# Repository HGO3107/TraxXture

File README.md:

# 🚀 TaxXture – The Tracker with Capturing Features
A tracking device with **remote interior capturing capabilty**

## 🔥 Features  
- **Real-time location tracking** – Get your vehicle’s location on demand  
- **Motion sensing & speed monitoring** – Know when your vehicle is on the move  
- **Battery Backup and health monitoring** – Keep track of power levels  
- **Remote interior capturing** – Snap image of your vehicle’s interior when needed  
- **Offline storage** – Data backup, even without an internet connection  
- **Reverse polarity protection** – To ensure the device does not get affected should incase the vehicle pollarity is mistakenly swapped  

## 🏗️ Project Structure  
📂 **Main Board** – The brains of the operation
📂 **Cam-Interconnect Board** – The bridge between the camera and the system  
📂 **Rendered Images** – Stunning visuals of the design  

## 🔧 Main Board – What's Inside?  
The **Main Board** packs all the essentials:  
✅ **Microcontroller, sensors, and actuator circuitry**  
✅ **LVDS driver/receiver port** – Ensures **3-5m** long-distance camera communication  

## 📸 Cam-Interconnect Board  
This board connects the camera to the system using:  
✅ **LVDS to SPI converter**  
✅ **Camera port connector**  

## 🚧 Disclaimer; Work in Progress (Status: **DRAFT** 🚀)  
Still some work to do, Below are what I could think of, you can pick it up from here if insterested:  

🔲 **Generate BOM & Fabrication files**  
🔲 **Review schematics & PCB layouts**  
🔲 **Complete the Cam-Interconnect Board:**  
   - PCB layout  
   - Electrical Rule Check (ERC) & Design Rule Check (DRC)  
🔲 **Finalize the enclosure design** (Done in FreeCAD but needs tweaks for connectors)  

## 📷 Main Board Images  

[📄 View Documentation](Hardware/Main-Board/TraxXturE_board.pdf)

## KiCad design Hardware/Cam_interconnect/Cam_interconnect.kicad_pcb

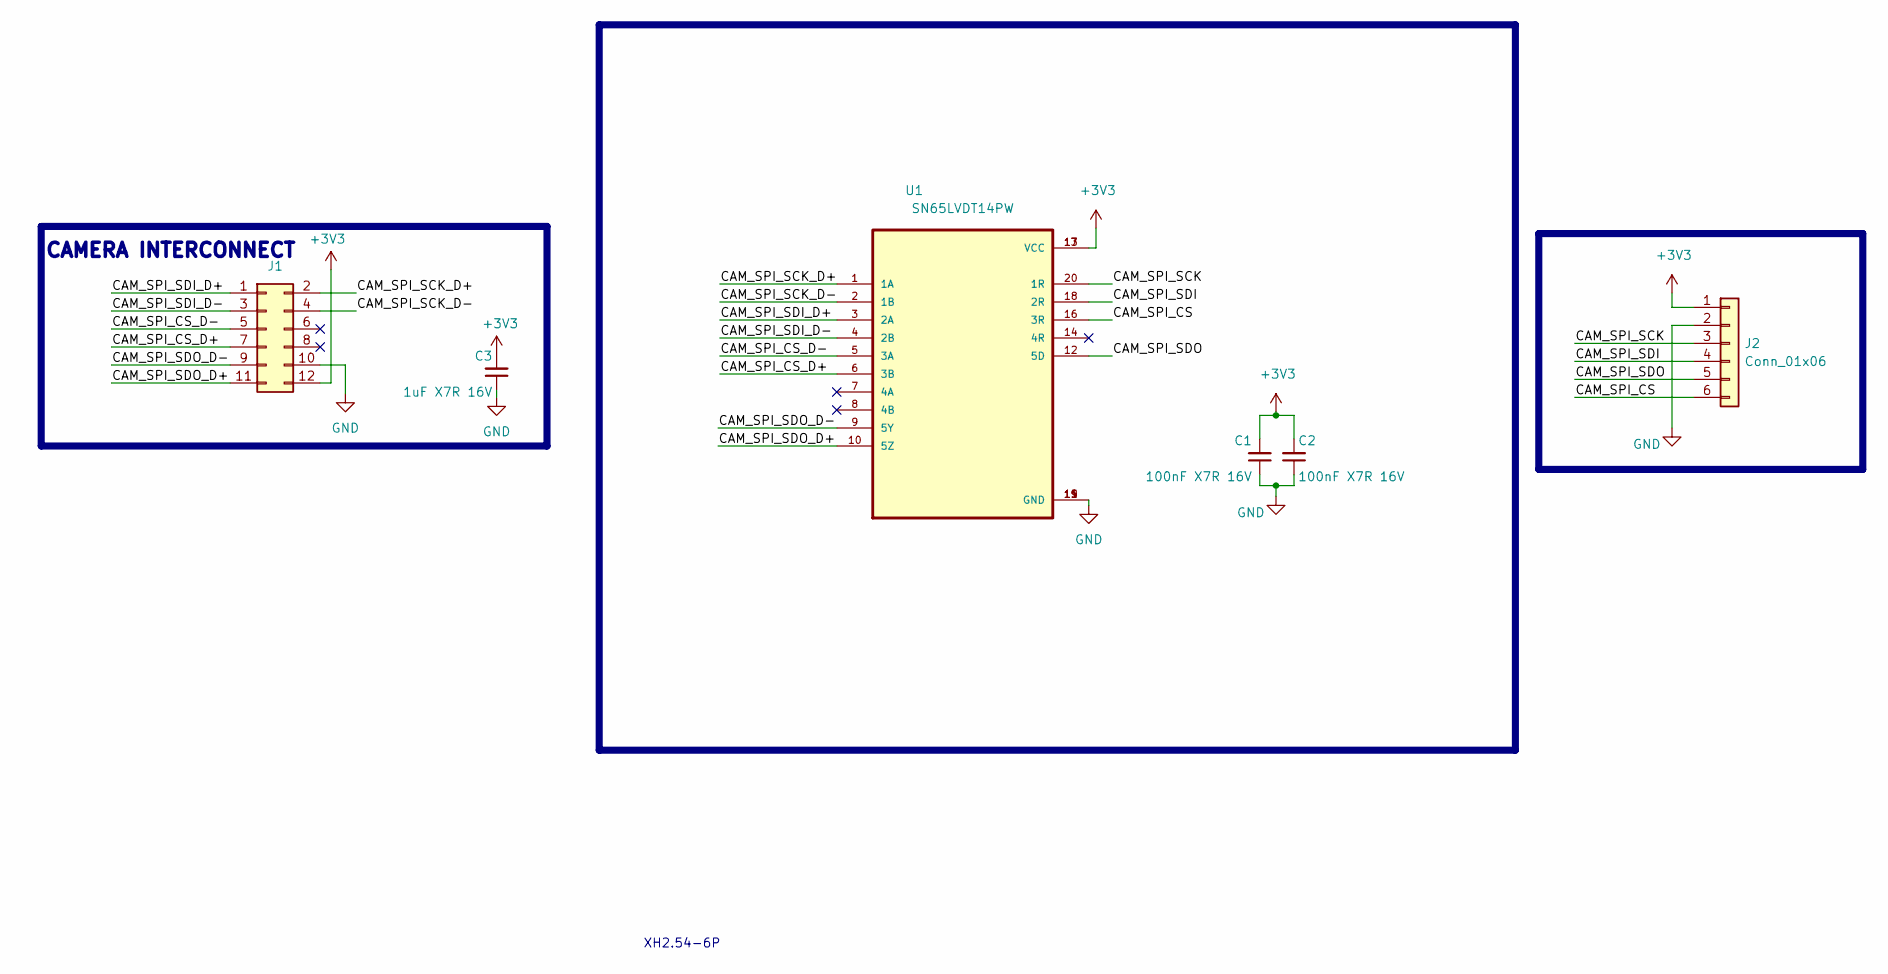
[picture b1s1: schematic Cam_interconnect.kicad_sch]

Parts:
C1, C2: 100nF X7R 16V; C_0402_1005Metric
C3: 1uF X7R 16V; C_0402_1005Metric
J1: Conn_02x06_Odd_Even; JST_PHD_S12B-PHDSS_2x06_P2.00mm_Horizontal
J2: Conn_01x06; PinSocket_1x06_P2.54mm_Vertical_SMD_Pin1Right
U1: SN65LVDT14PW; SOP65P640X120-20N

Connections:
+3V3: C1.2, C2.2, C3.2, J1.12, J2.1, U1.13 (VCC), U1.17 (VCC)
/CAM_SPI_CS: J2.6, U1.16 (3R)
/CAM_SPI_CS_D+: J1.7, U1.6 (3B)
/CAM_SPI_CS_D-: J1.5, U1.5 (3A)
/CAM_SPI_SCK: J2.3, U1.20 (1R)
/CAM_SPI_SCK_D+: J1.2, U1.1 (1A)
/CAM_SPI_SCK_D-: J1.4, U1.2 (1B)
/CAM_SPI_SDI: J2.4, U1.18 (2R)
/CAM_SPI_SDI_D+: J1.1, U1.3 (2A)
/CAM_SPI_SDI_D-: J1.3, U1.4 (2B)
/CAM_SPI_SDO: J2.5, U1.12 (5D)
/CAM_SPI_SDO_D+: J1.11, U1.10 (5Z)
/CAM_SPI_SDO_D-: J1.9, U1.9 (5Y)
GND: C1.1, C2.1, C3.1, J1.10, J2.2, U1.11 (GND), U1.15 (GND), U1.19 (GND)

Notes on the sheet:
XH2.54-6P
CAMERA INTERCONNECT

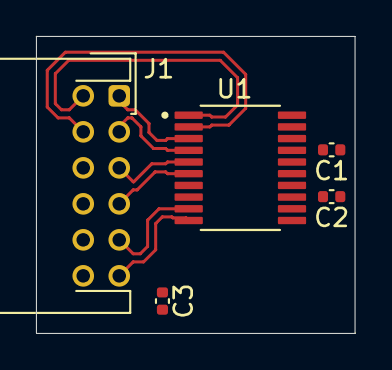
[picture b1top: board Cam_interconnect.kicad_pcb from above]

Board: 4 copper layers, 17.7 x 16.5 mm, 6 parts (1 on the bottom side), 14 nets.

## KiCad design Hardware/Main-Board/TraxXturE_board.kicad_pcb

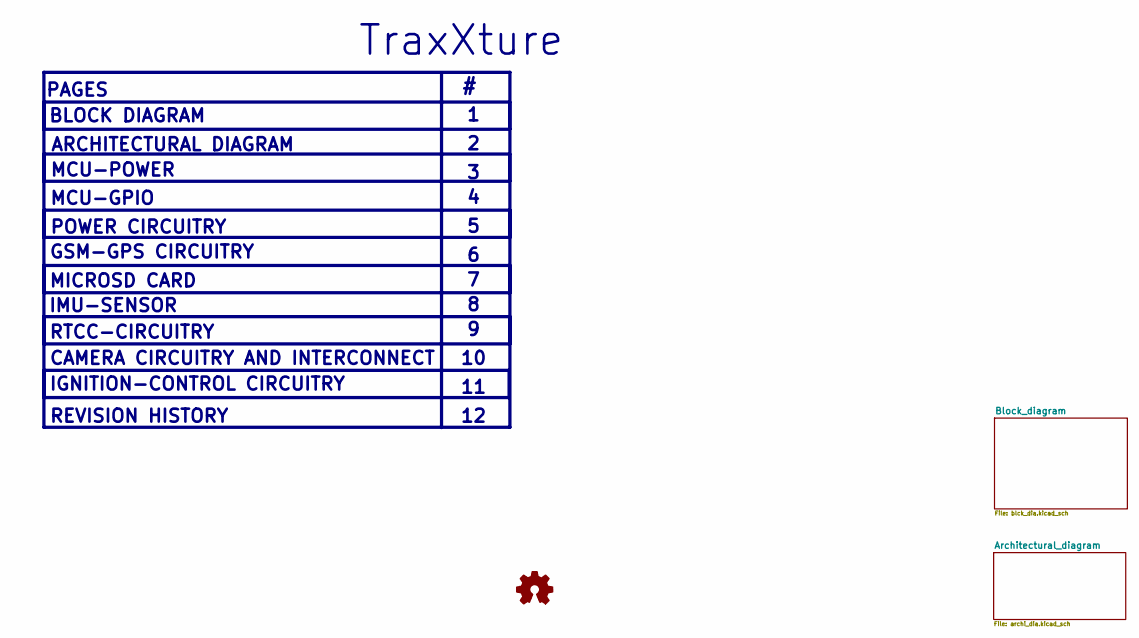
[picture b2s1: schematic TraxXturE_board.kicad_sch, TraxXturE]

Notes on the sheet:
IMU-SENSOR
MCU-POWER
MICROSD CARD
ARCHITECTURAL DIAGRAM
PAGES
RTCC-CIRCUITRY
CAMERA CIRCUITRY AND INTERCONNECT
BLOCK DIAGRAM
POWER CIRCUITRY
GSM-GPS CIRCUITRY
REVISION HISTORY
MCU-GPIO
IGNITION-CONTROL CIRCUITRY
TraxXture

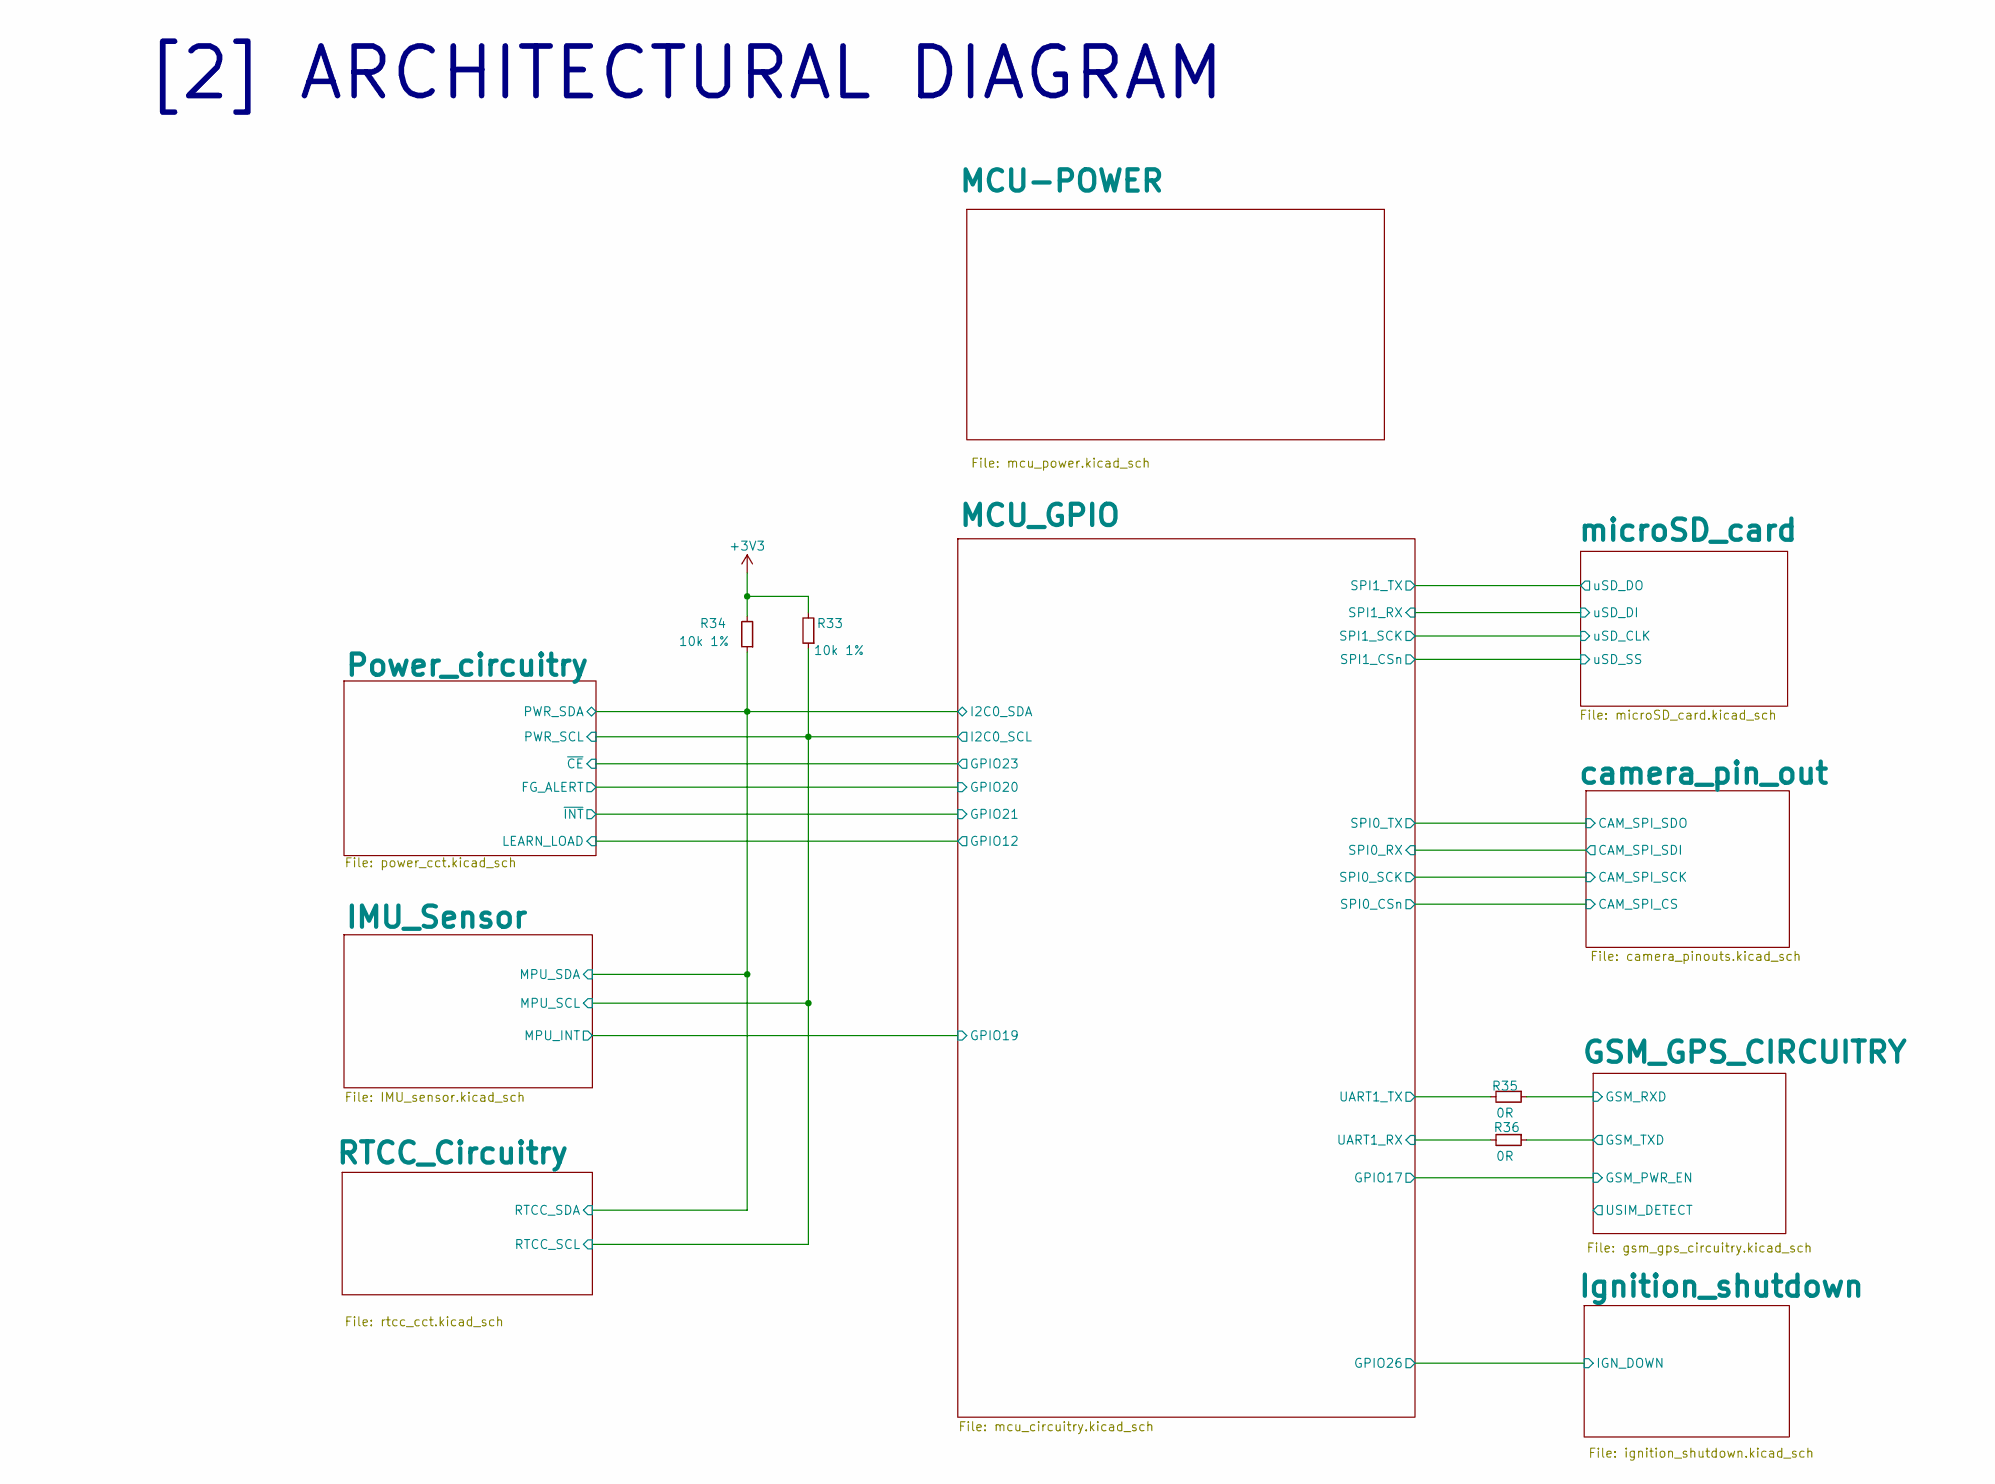
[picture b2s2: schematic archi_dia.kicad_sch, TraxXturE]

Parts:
R33, R34: 10k 1%; R_0402_1005Metric
R35, R36: 0R; R_0402_1005Metric

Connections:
+3V3: R33.2, R34.2; also elsewhere on the board
/Architectural_diagram/GSM_GPS_CIRCUITRY/GSM_RXD: R35.1; also elsewhere on the board
/Architectural_diagram/GSM_GPS_CIRCUITRY/GSM_TXD: R36.1; also elsewhere on the board
/Architectural_diagram/IMU_Sensor/MPU_SCL: R33.1; also elsewhere on the board
/Architectural_diagram/IMU_Sensor/MPU_SDA: R34.1; also elsewhere on the board
/Architectural_diagram/MCU_GPIO/UART1_RX: R36.2; also elsewhere on the board
/Architectural_diagram/MCU_GPIO/UART1_TX: R35.2; also elsewhere on the board

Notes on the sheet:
[2] ARCHITECTURAL DIAGRAM

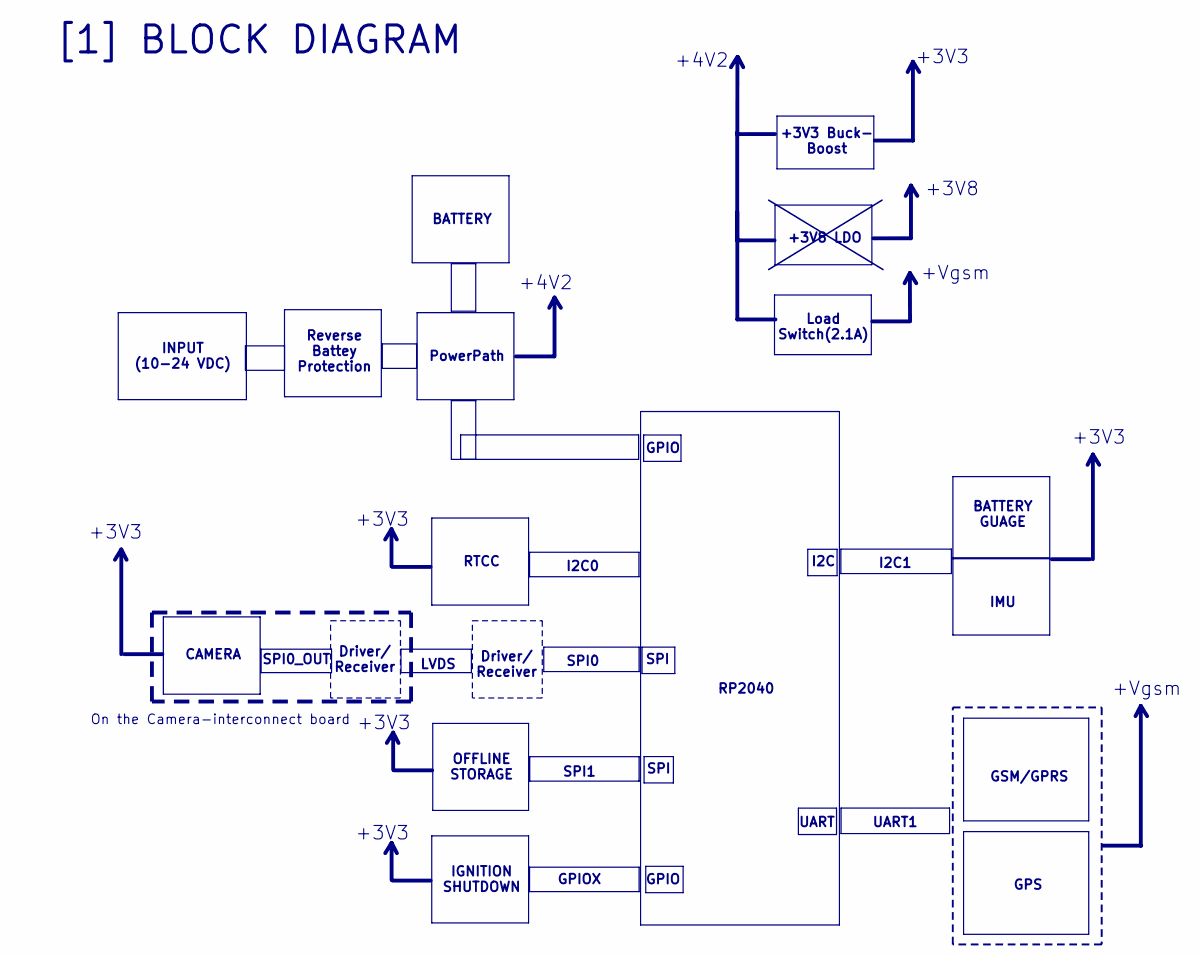
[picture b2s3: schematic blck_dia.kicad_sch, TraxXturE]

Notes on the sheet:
SPI0_OUT
+3V3
SPI
I2C
OFFLINE STORAGE
+3V8
I2C0
GPIO
UART
BATTERY
CAMERA
GSM/GPRS
INPUT (10-24 VDC)
Driver/ Receiver
I2C1
+3V8 LDO
IGNITION SHUTDOWN
BATTERY GUAGE
PowerPath
LVDS
SPI1
+3V3 Buck- Boost
SPI0
Reverse Battey Protection
+4V2
RTCC
On the Camera-interconnect board
+Vgsm
UART1
[1] BLOCK DIAGRAM
GPS
IMU
RP2040
GPIOX
Load Switch(2.1A)

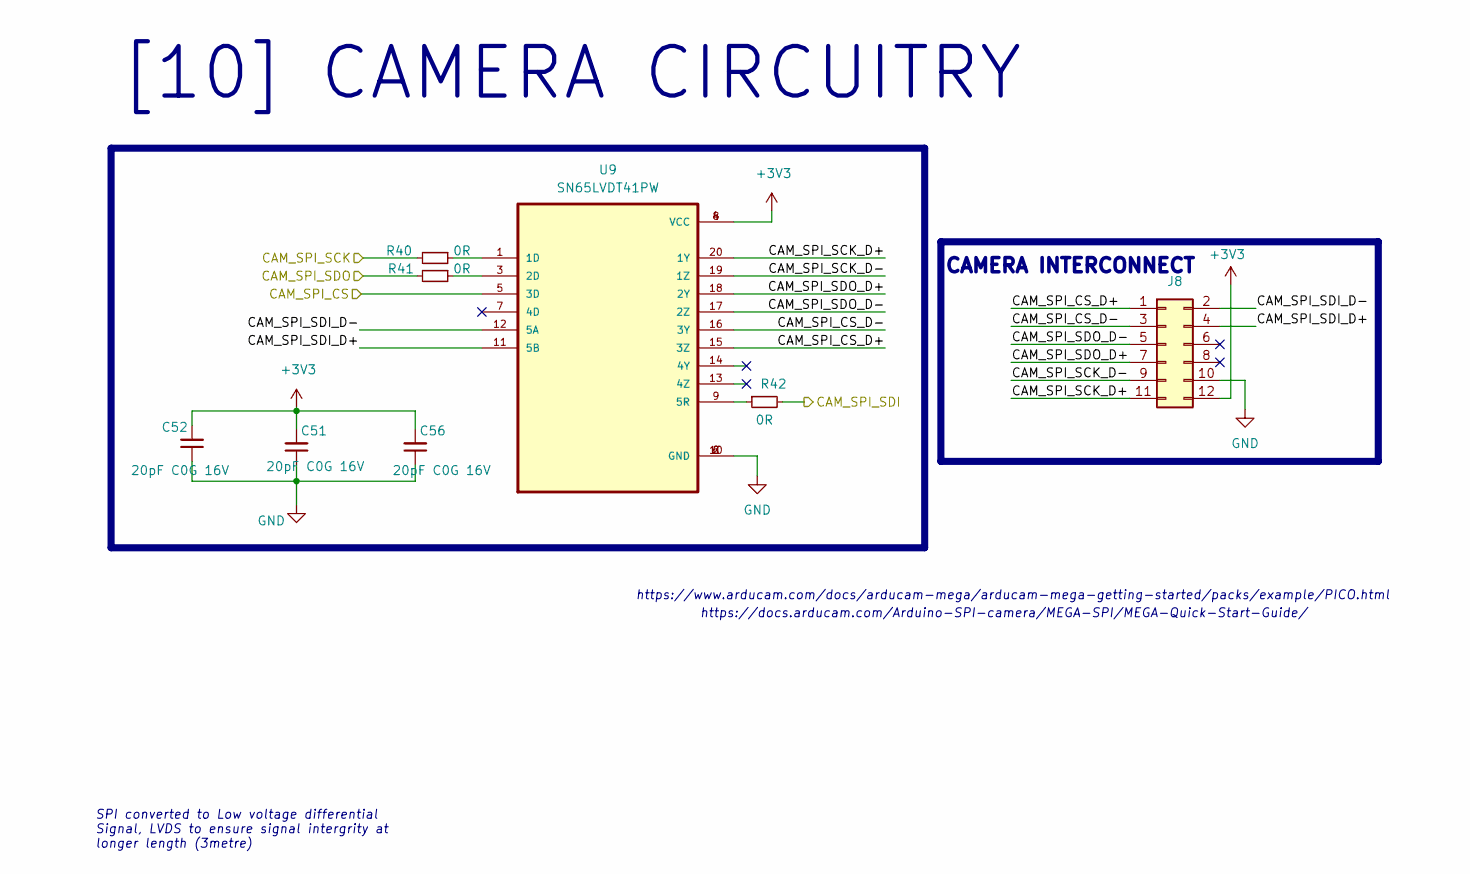
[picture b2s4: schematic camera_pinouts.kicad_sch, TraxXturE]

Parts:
C51, C52, C56: 20pF C0G 16V; C_0402_1005Metric
J8: Conn_02x06_Odd_Even; JST_PHD_S12B-PHDSS_2x06_P2.00mm_Horizontal
R40, R41, R42: 0R; R_0402_1005Metric
U9: SN65LVDT41PW; SOP65P640X120-20N

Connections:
+3V3: C51.2, C52.2, C56.2, J8.12, U9.4 (VCC), U9.8 (VCC); also elsewhere on the board
/Architectural_diagram/MCU_GPIO/SPI0_CSn: U9.5 (3D); also elsewhere on the board
/Architectural_diagram/MCU_GPIO/SPI0_RX: R42.2; also elsewhere on the board
/Architectural_diagram/MCU_GPIO/SPI0_SCK: R40.2; also elsewhere on the board
/Architectural_diagram/MCU_GPIO/SPI0_TX: R41.2; also elsewhere on the board
/Architectural_diagram/camera_pin_out/CAM_SPI_CS_D+: J8.1, U9.15 (3Z)
/Architectural_diagram/camera_pin_out/CAM_SPI_CS_D-: J8.3, U9.16 (3Y)
/Architectural_diagram/camera_pin_out/CAM_SPI_SCK_D+: J8.11, U9.20 (1Y)
/Architectural_diagram/camera_pin_out/CAM_SPI_SCK_D-: J8.9, U9.19 (1Z)
/Architectural_diagram/camera_pin_out/CAM_SPI_SDI_D+: J8.4, U9.11 (5B)
/Architectural_diagram/camera_pin_out/CAM_SPI_SDI_D-: J8.2, U9.12 (5A)
/Architectural_diagram/camera_pin_out/CAM_SPI_SDO_D+: J8.7, U9.18 (2Y)
/Architectural_diagram/camera_pin_out/CAM_SPI_SDO_D-: J8.5, U9.17 (2Z)
GND: C51.1, C52.1, C56.1, J8.10, U9.2 (GND), U9.6 (GND), U9.10 (GND); also elsewhere on the board
unnamed: R40.1, U9.1 (1D)
unnamed: R41.1, U9.3 (2D)
unnamed: R42.1, U9.9 (5R)

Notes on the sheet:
https://www.arducam.com/docs/arducam-mega/arducam-mega-getting-started/packs/example/PICO.html
SPI converted to Low voltage differential Signal, LVDS to ensure signal intergrity at longer length (3metre)
https://docs.arducam.com/Arduino-SPI-camera/MEGA-SPI/MEGA-Quick-Start-Guide/
CAMERA INTERCONNECT
[10] CAMERA CIRCUITRY

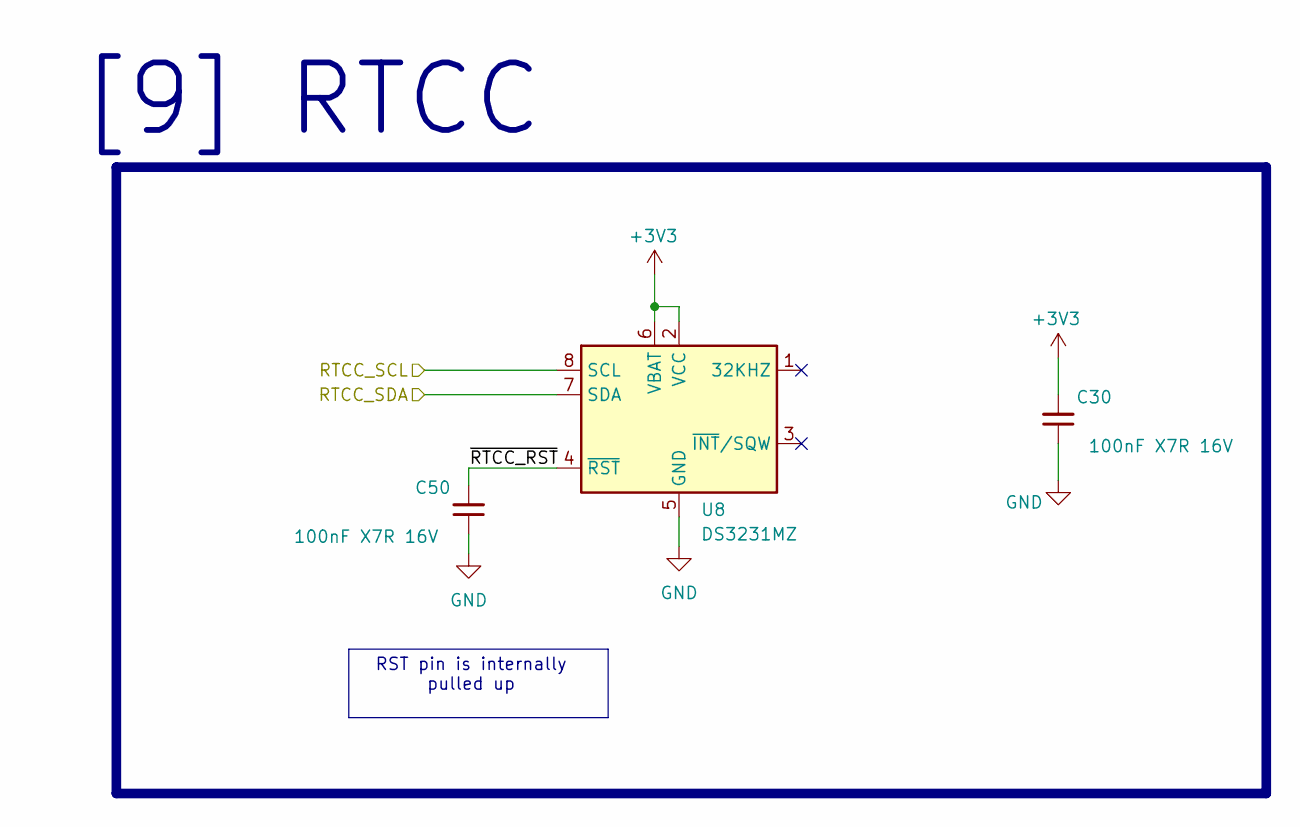
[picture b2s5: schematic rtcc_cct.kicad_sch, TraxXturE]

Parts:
C30, C50: 100nF X7R 16V; C_0402_1005Metric
U8: DS3231MZ; SOIC-8_3.9x4.9mm_P1.27mm

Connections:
+3V3: C30.2, U8.2 (VCC), U8.6 (VBAT); also elsewhere on the board
/Architectural_diagram/IMU_Sensor/MPU_SCL: U8.8 (SCL); also elsewhere on the board
/Architectural_diagram/IMU_Sensor/MPU_SDA: U8.7 (SDA); also elsewhere on the board
/Architectural_diagram/RTCC_Circuitry/~RTCC_RST: C50.2, U8.4 (~RST)
GND: C30.1, C50.1, U8.5 (GND); also elsewhere on the board

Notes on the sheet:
RST pin is internally pulled up
[9] RTCC

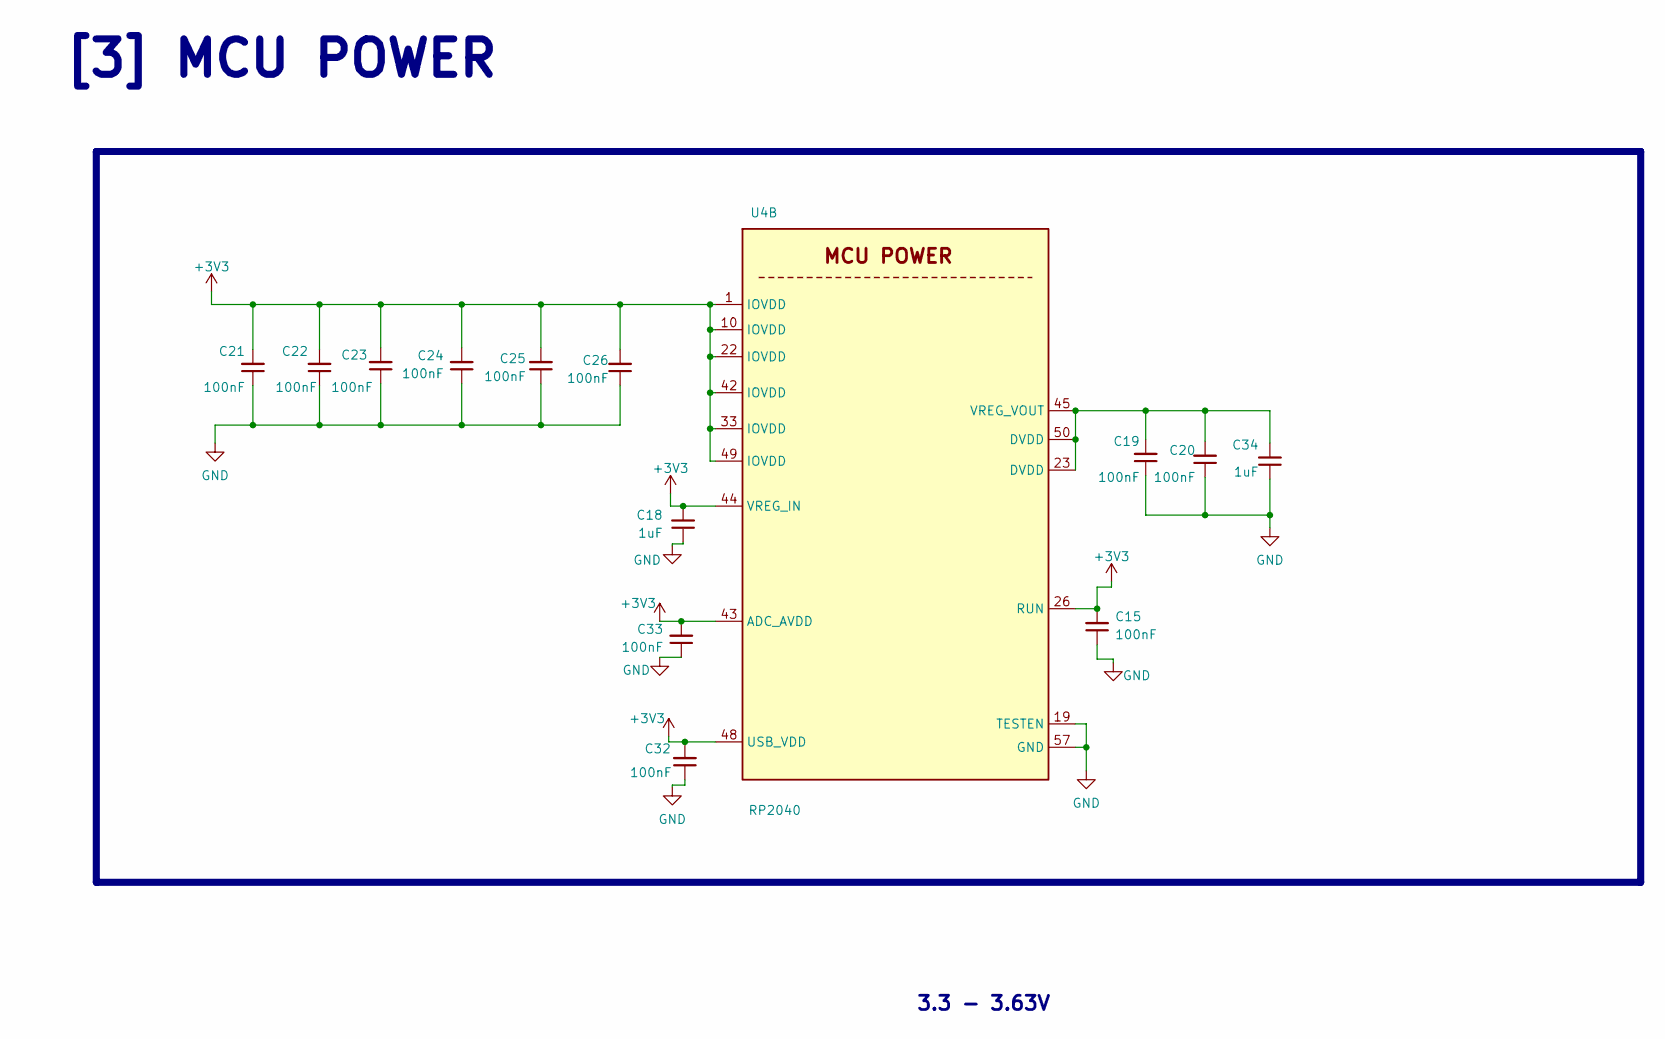
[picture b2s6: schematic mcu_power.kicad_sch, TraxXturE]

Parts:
C15, C19, C20, C21, C22, C23, C24, C25, C26, C32, C33: 100nF; C_0402_1005Metric
C18, C34: 1uF; C_0402_1005Metric
U4: RP2040; QFN-56-1EP_7x7mm_P0.4mm_EP3.2x3.2mm

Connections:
+3V3: C15.2, C18.2, C21.2, C22.2, C23.2, C24.2, C25.2, C26.2, C32.2, C33.2, U4.1 (IOVDD), U4.10 (IOVDD), U4.22 (IOVDD), U4.26 (RUN), U4.33 (IOVDD), U4.42 (IOVDD), U4.43 (ADC_AVDD), U4.44 (VREG_IN), U4.48 (USB_VDD), U4.49 (IOVDD); also elsewhere on the board
GND: C15.1, C18.1, C19.1, C20.1, C21.1, C22.1, C23.1, C24.1, C25.1, C26.1, C32.1, C33.1, C34.1, U4.19 (TESTEN), U4.57 (GND); also elsewhere on the board
unnamed: C19.2, C20.2, C34.2, U4.23 (DVDD), U4.45 (VREG_VOUT), U4.50 (DVDD)

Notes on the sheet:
[3] MCU POWER
3.3 - 3.63V

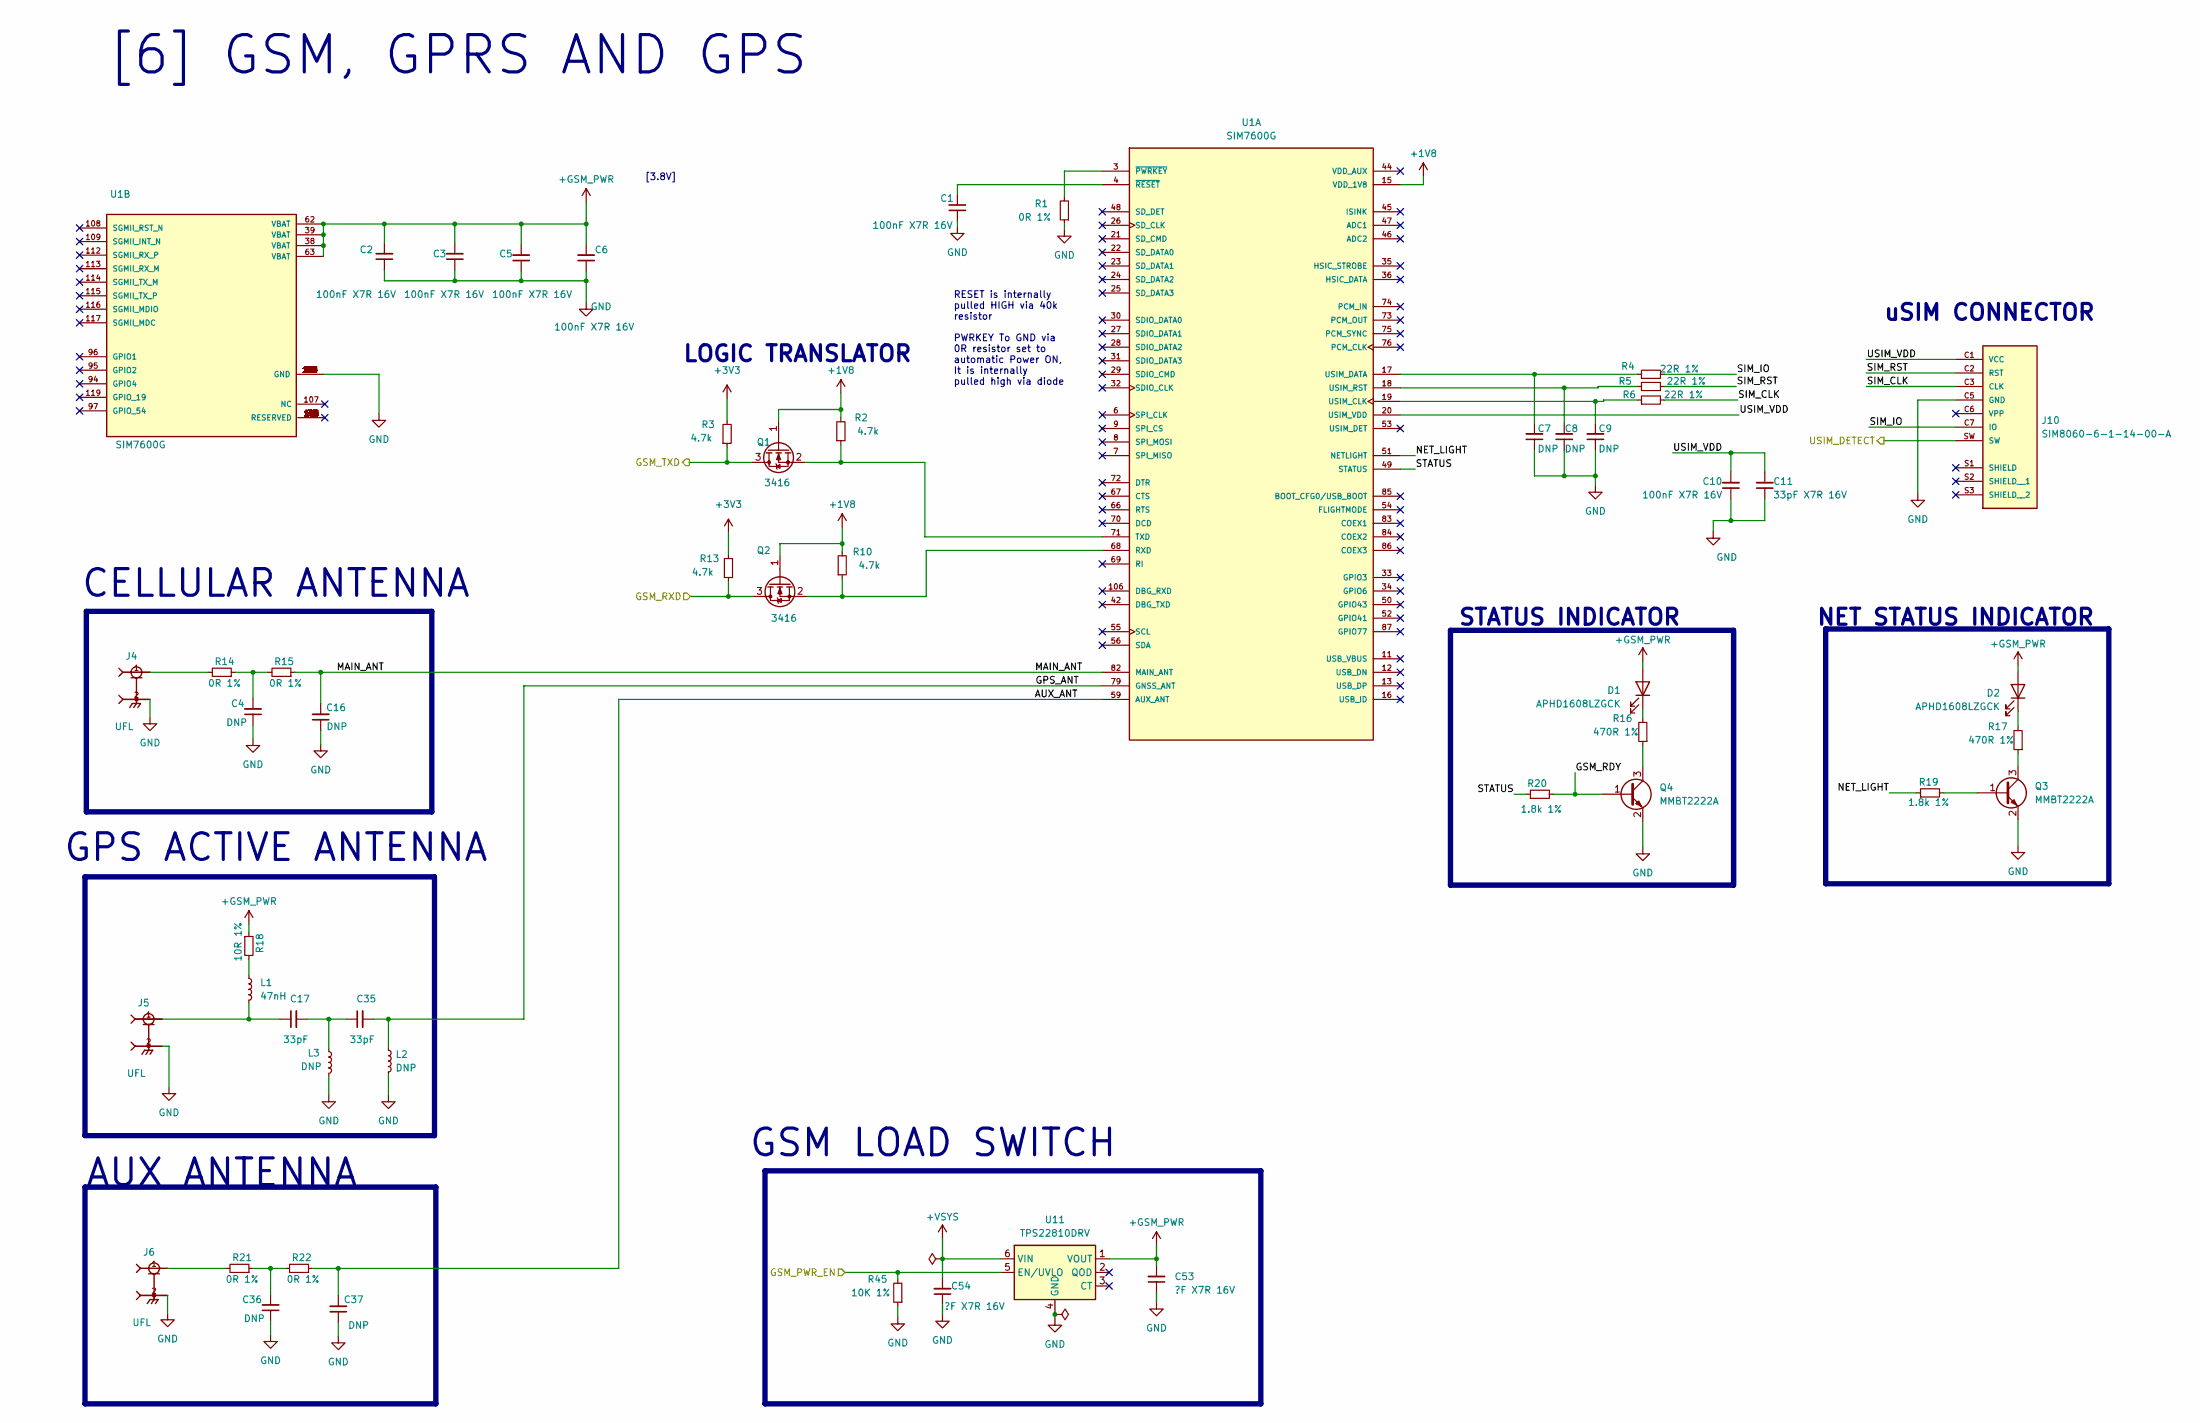
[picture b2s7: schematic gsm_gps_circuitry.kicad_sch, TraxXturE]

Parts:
C1, C2, C3, C5, C6, C10: 100nF X7R 16V; C_0402_1005Metric
C4, C16, C36, C37: DNP; C_0603_1608Metric
C7, C8, C9: DNP; C_0402_1005Metric
C11: 33pF X7R 16V; C_0402_1005Metric
C17, C35: 33pF; C_0603_1608Metric
C53, C54: ?F X7R 16V; C_0402_1005Metric
D1, D2: APHD1608LZGCK; LED_0603_1608Metric
J4, J5, J6: UFL; HRS_U.FL-R-SMT_10_
J10: SIM8060-6-1-14-00-A; GCT_SIM8060-6-1-14-00-A; PARTREV A
L1: 47nH; L_0603_1608Metric
L2, L3: DNP; L_0603_1608Metric
Q1, Q2: 3416; SOT-23
Q3, Q4: MMBT2222A; SOT-23
R1, R14, R15, R21, R22: 0R 1%; R_0402_1005Metric
R2, R3, R10, R13: 4.7k; R_0402_1005Metric
R4, R5, R6: 22R 1%; R_0402_1005Metric
R16, R17: 470R 1%; R_0402_1005Metric
R18: 10R 1%; R_0402_1005Metric
R19, R20: 1.8k 1%; R_0402_1005Metric
R45: 10K 1%; R_0402_1005Metric
U1: SIM7600G; IC_SIM7600G
U11: TPS22810DRV; WSON-6-1EP_2x2mm_P0.65mm_EP1x1.6mm

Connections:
+1V8: Q1.1 (G), Q2.1 (G), R2.2, R10.2, U1.15 (VDD_1V8)
+3V3: R3.2, R13.2; also elsewhere on the board
+GSM_PWR: C2.2, C3.2, C5.2, C6.2, C53.2, D1.2 (A), D2.2 (A), R18.1, U1.38 (VBAT), U1.39 (VBAT), U1.62 (VBAT), U1.63 (VBAT), U11.1 (VOUT)
+VSYS: C54.2, U11.6 (VIN); also elsewhere on the board
/Architectural_diagram/GSM_GPS_CIRCUITRY/AUX_ANT: C37.2, R22.1, U1.59 (AUX_ANT)
/Architectural_diagram/GSM_GPS_CIRCUITRY/GPS_ANT: C35.2, L2.1, U1.79 (GNSS_ANT)
/Architectural_diagram/GSM_GPS_CIRCUITRY/GSM_PWR_EN: R45.2, U11.5 (EN/UVLO); also elsewhere on the board
/Architectural_diagram/GSM_GPS_CIRCUITRY/GSM_RDY: Q4.1 (B), R20.2
/Architectural_diagram/GSM_GPS_CIRCUITRY/GSM_RXD: Q2.3 (D), R13.1; also elsewhere on the board
/Architectural_diagram/GSM_GPS_CIRCUITRY/GSM_TXD: Q1.3 (D), R3.1; also elsewhere on the board
/Architectural_diagram/GSM_GPS_CIRCUITRY/MAIN_ANT: C16.2, R15.1, U1.82 (MAIN_ANT)
/Architectural_diagram/GSM_GPS_CIRCUITRY/NET_LIGHT: R19.1, U1.51 (NETLIGHT)
/Architectural_diagram/GSM_GPS_CIRCUITRY/SIM_CLK: J10.C3 (CLK), R6.2
/Architectural_diagram/GSM_GPS_CIRCUITRY/SIM_IO: J10.C7 (IO), R4.2
/Architectural_diagram/GSM_GPS_CIRCUITRY/SIM_RST: J10.C2 (RST), R5.2
/Architectural_diagram/GSM_GPS_CIRCUITRY/STATUS: R20.1, U1.49 (STATUS)
/Architectural_diagram/GSM_GPS_CIRCUITRY/USIM_DETECT: J10.SW
/Architectural_diagram/GSM_GPS_CIRCUITRY/USIM_VDD: C10.2, C11.2, J10.C1 (VCC), U1.20 (USIM_VDD)
GND: C1.1, C2.1, C3.1, C4.1, C5.1, C6.1, C7.1, C8.1, C9.1, C10.1, C11.1, C16.1, C36.1, C37.1, C53.1, C54.1, J4.2, J5.2, J6.2, J10.C5 (GND), L2.2, L3.2, Q3.2 (E), Q4.2 (E), R1.1, R45.1, U1.1 (GND), U1.2 (GND), U1.5 (GND), U1.10 (GND), U1.14 (GND), U1.37 (GND), U1.40 (GND), U1.41 (GND), U1.43 (GND), U1.57 (GND), U1.58 (GND), U1.60 (GND), U1.61 (GND), U1.64 (GND), U1.65 (GND), U1.77 (GND), U1.78 (GND), U1.80 (GND), U1.81 (GND), U1.93 (GND), U1.98 (GND), U1.110 (GND), U1.118 (GND), U1.120 (GND), U1.121 (GND), U1.122 (GND), U1.123 (GND), U1.124 (GND), U1.125 (GND), U1.126 (GND), U1.127 (GND), U1.128 (GND), U1.129 (GND), U1.130 (GND), U1.131 (GND), U1.132 (GND), U1.133 (GND), U1.134 (GND), U1.135 (GND), U11.4 (GND), U11.7 (GND); also elsewhere on the board
unnamed: C4.2, R14.1, R15.2
unnamed: C17.1, J5.1, L1.2
unnamed: C17.2, C35.1, L3.1
unnamed: C36.2, R21.1, R22.2
unnamed: D1.1 (K), R16.2
unnamed: D2.1 (K), R17.2
unnamed: J4.1, R14.2
unnamed: J6.1, R21.2
unnamed: L1.1, R18.2
unnamed: Q1.2 (S), R2.1, U1.71 (TXD)
unnamed: Q2.2 (S), R10.1, U1.68 (RXD)
unnamed: Q3.1 (B), R19.2
unnamed: Q3.3 (C), R17.1
unnamed: Q4.3 (C), R16.1
unnamed: C9.2, R6.1, U1.19 (USIM_CLK)
unnamed: C7.2, R4.1, U1.17 (USIM_DATA)
unnamed: C8.2, R5.1, U1.18 (USIM_RST)
unnamed: R1.2, U1.3 (~PWRKEY)
unnamed: C1.2, U1.4 (~RESET)

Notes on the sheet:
RESET is internally pulled HIGH via 40k resistor
PWRKEY To GND via 0R resistor set to automatic Power ON, It is internally pulled high via diode
[6] GSM, GPRS AND GPS
CELLULAR ANTENNA
STATUS INDICATOR
NET STATUS INDICATOR
GSM LOAD SWITCH
uSIM CONNECTOR
GPS ACTIVE ANTENNA
AUX ANTENNA
LOGIC TRANSLATOR
[3.8V]

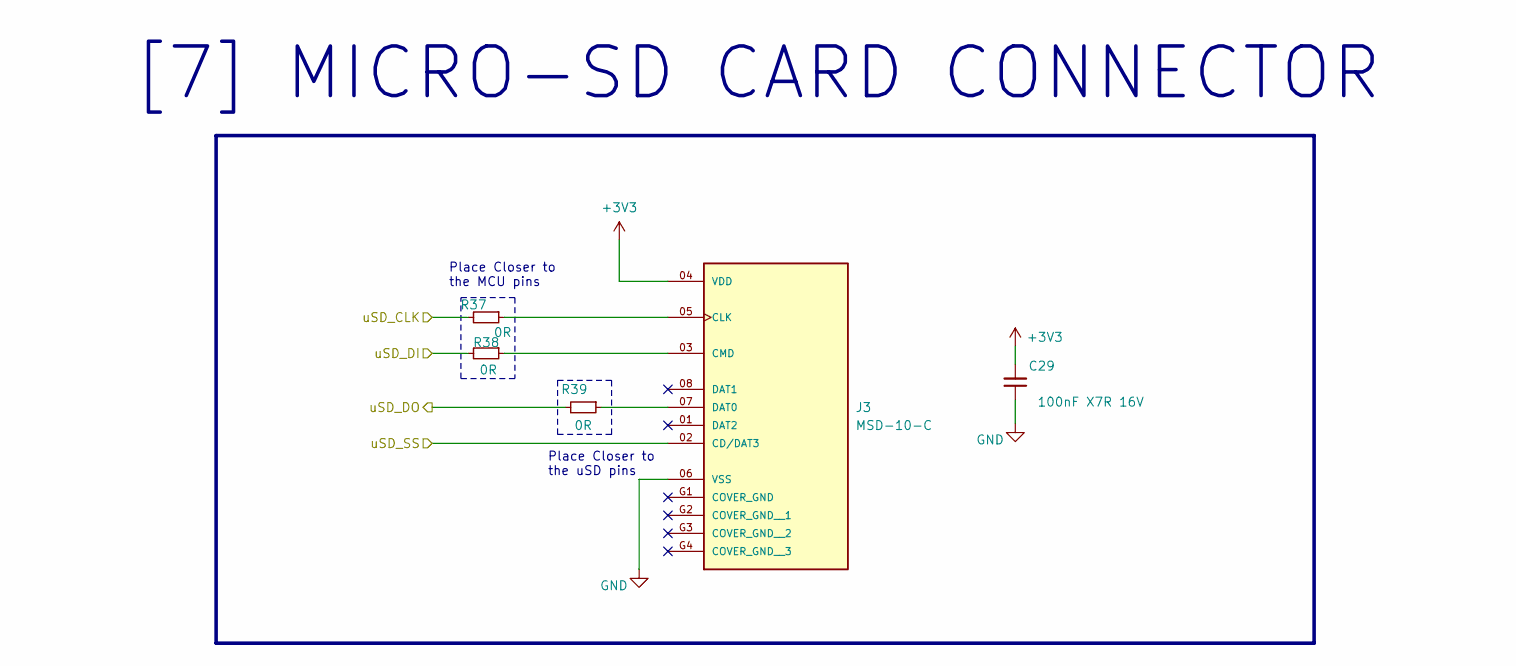
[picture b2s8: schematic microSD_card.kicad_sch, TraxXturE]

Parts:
C29: 100nF X7R 16V; C_0402_1005Metric
J3: MSD-10-C; CUI_MSD-10-C; PARTREV 1.0
R37, R38, R39: 0R; R_0402_1005Metric

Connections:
+3V3: C29.2, J3.04 (VDD); also elsewhere on the board
/Architectural_diagram/MCU_GPIO/SPI1_CSn: J3.02 (CD/DAT3); also elsewhere on the board
/Architectural_diagram/MCU_GPIO/SPI1_RX: R38.2; also elsewhere on the board
/Architectural_diagram/MCU_GPIO/SPI1_SCK: R37.2; also elsewhere on the board
/Architectural_diagram/MCU_GPIO/SPI1_TX: R39.2; also elsewhere on the board
GND: C29.1, J3.06 (VSS); also elsewhere on the board
unnamed: J3.05 (CLK), R37.1
unnamed: J3.03 (CMD), R38.1
unnamed: J3.07 (DAT0), R39.1

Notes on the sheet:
Place Closer to the uSD pins
Place Closer to the MCU pins
[7] MICRO-SD CARD CONNECTOR

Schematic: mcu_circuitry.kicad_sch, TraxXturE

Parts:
C12: 100nF; C_0402_1005Metric
C13, C14: 15pF; C_0402_1005Metric
J1: Conn_01x06; PinHeader_2x03_P2.54mm_Vertical
R9: 1k; R_0402_1005Metric
U3: W25Q128JVS; SOIC-8_5.23x5.23mm_P1.27mm
U4: RP2040; QFN-56-1EP_7x7mm_P0.4mm_EP3.2x3.2mm
Y1: ABM8-272-T3; ABM8-272-T3_ABR

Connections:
+3V3: C12.2, J1.1, U3.8 (VCC); also elsewhere on the board
/Architectural_diagram/GSM_GPS_CIRCUITRY/GSM_PWR_EN: U4.29 (GPIO18); also elsewhere on the board
/Architectural_diagram/IMU_Sensor/MPU_INT: U4.30 (GPIO19); also elsewhere on the board
/Architectural_diagram/IMU_Sensor/MPU_SCL: U4.17 (GPIO14); also elsewhere on the board
/Architectural_diagram/IMU_Sensor/MPU_SDA: U4.16 (GPIO13); also elsewhere on the board
/Architectural_diagram/Ignition_shutdown/IGN_DOWN: U4.38 (GPIO26_ADC0); also elsewhere on the board
/Architectural_diagram/MCU_GPIO/GPIO12: U4.15 (GPIO12); also elsewhere on the board
/Architectural_diagram/MCU_GPIO/GPIO20: U4.31 (GPIO20); also elsewhere on the board
/Architectural_diagram/MCU_GPIO/GPIO21: U4.32 (GPIO21); also elsewhere on the board
/Architectural_diagram/MCU_GPIO/GPIO23: U4.35 (GPIO23); also elsewhere on the board
/Architectural_diagram/MCU_GPIO/SPI0_CSn: U4.3 (GPIO1); also elsewhere on the board
/Architectural_diagram/MCU_GPIO/SPI0_RX: U4.2 (GPIO0); also elsewhere on the board
/Architectural_diagram/MCU_GPIO/SPI0_SCK: U4.4 (GPIO2); also elsewhere on the board
/Architectural_diagram/MCU_GPIO/SPI0_TX: U4.5 (GPIO3); also elsewhere on the board
/Architectural_diagram/MCU_GPIO/SPI1_CSn: U4.12 (GPIO9); also elsewhere on the board
/Architectural_diagram/MCU_GPIO/SPI1_RX: U4.11 (GPIO8); also elsewhere on the board
/Architectural_diagram/MCU_GPIO/SPI1_SCK: U4.13 (GPIO10); also elsewhere on the board
/Architectural_diagram/MCU_GPIO/SPI1_TX: U4.14 (GPIO11); also elsewhere on the board
/Architectural_diagram/MCU_GPIO/SWCLK: J1.2, U4.24 (SWCLK)
/Architectural_diagram/MCU_GPIO/SWD: J1.3, U4.25 (SWD)
/Architectural_diagram/MCU_GPIO/UART0_RX: J1.4, U4.28 (GPIO17)
/Architectural_diagram/MCU_GPIO/UART0_TX: J1.5, U4.27 (GPIO16)
/Architectural_diagram/MCU_GPIO/UART1_RX: U4.37 (GPIO25); also elsewhere on the board
/Architectural_diagram/MCU_GPIO/UART1_TX: U4.36 (GPIO24); also elsewhere on the board
GND: C12.1, C13.1, C14.1, J1.6, U3.4 (GND), Y1.2, Y1.4; also elsewhere on the board
unnamed: C13.2, R9.1, Y1.3
unnamed: U3.6 (CLK), U4.52 (QSPI_SCLK)
unnamed: U3.5 (DI(IO0)), U4.53 (QSPI_SD0)
unnamed: U3.2 (DO(IO1)), U4.55 (QSPI_SD1)
unnamed: U3.3 (IO2), U4.54 (QSPI_SD2)
unnamed: U3.7 (IO3), U4.51 (QSPI_SD3)
unnamed: U3.1 (~CS), U4.56 (QSPI_SS)
unnamed: C14.2, U4.20 (XIN), Y1.1
unnamed: R9.2, U4.21 (XOUT)

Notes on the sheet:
EXTERNAL FLASH MEMORY
DEBUG/PROG
[4] MCU GPIO
